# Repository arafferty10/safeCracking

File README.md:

# Team TAL: ATLS 4519 Safecracking Fall 2018
#### Repo for SafeCracking Class -- Using Arduino and manufactured parts to open a Sentry Safe Dial Safe

###### Successful Opening Video

## Information

Parts List - https://docs.google.com/spreadsheets/d/1XabOUtS-7bFRwG6XeN5u8nKVINY24XkEVGik6j0RJdE/edit?usp=sharing  
3D Printed Models - https://github.com/arafferty10/safeCracking/tree/master/models

## Personal Repos
* Lou - https://github.com/lume2651/safe-cracking 
* Aidan - https://github.com/arafferty10/personalSafeCracking
* Toby - https://github.com/towu1344/Safe-Cracking

## Images

---
Video of final opening: https://github.com/arafferty10/safeCracking/blob/master/img/IMG_3121.mp4

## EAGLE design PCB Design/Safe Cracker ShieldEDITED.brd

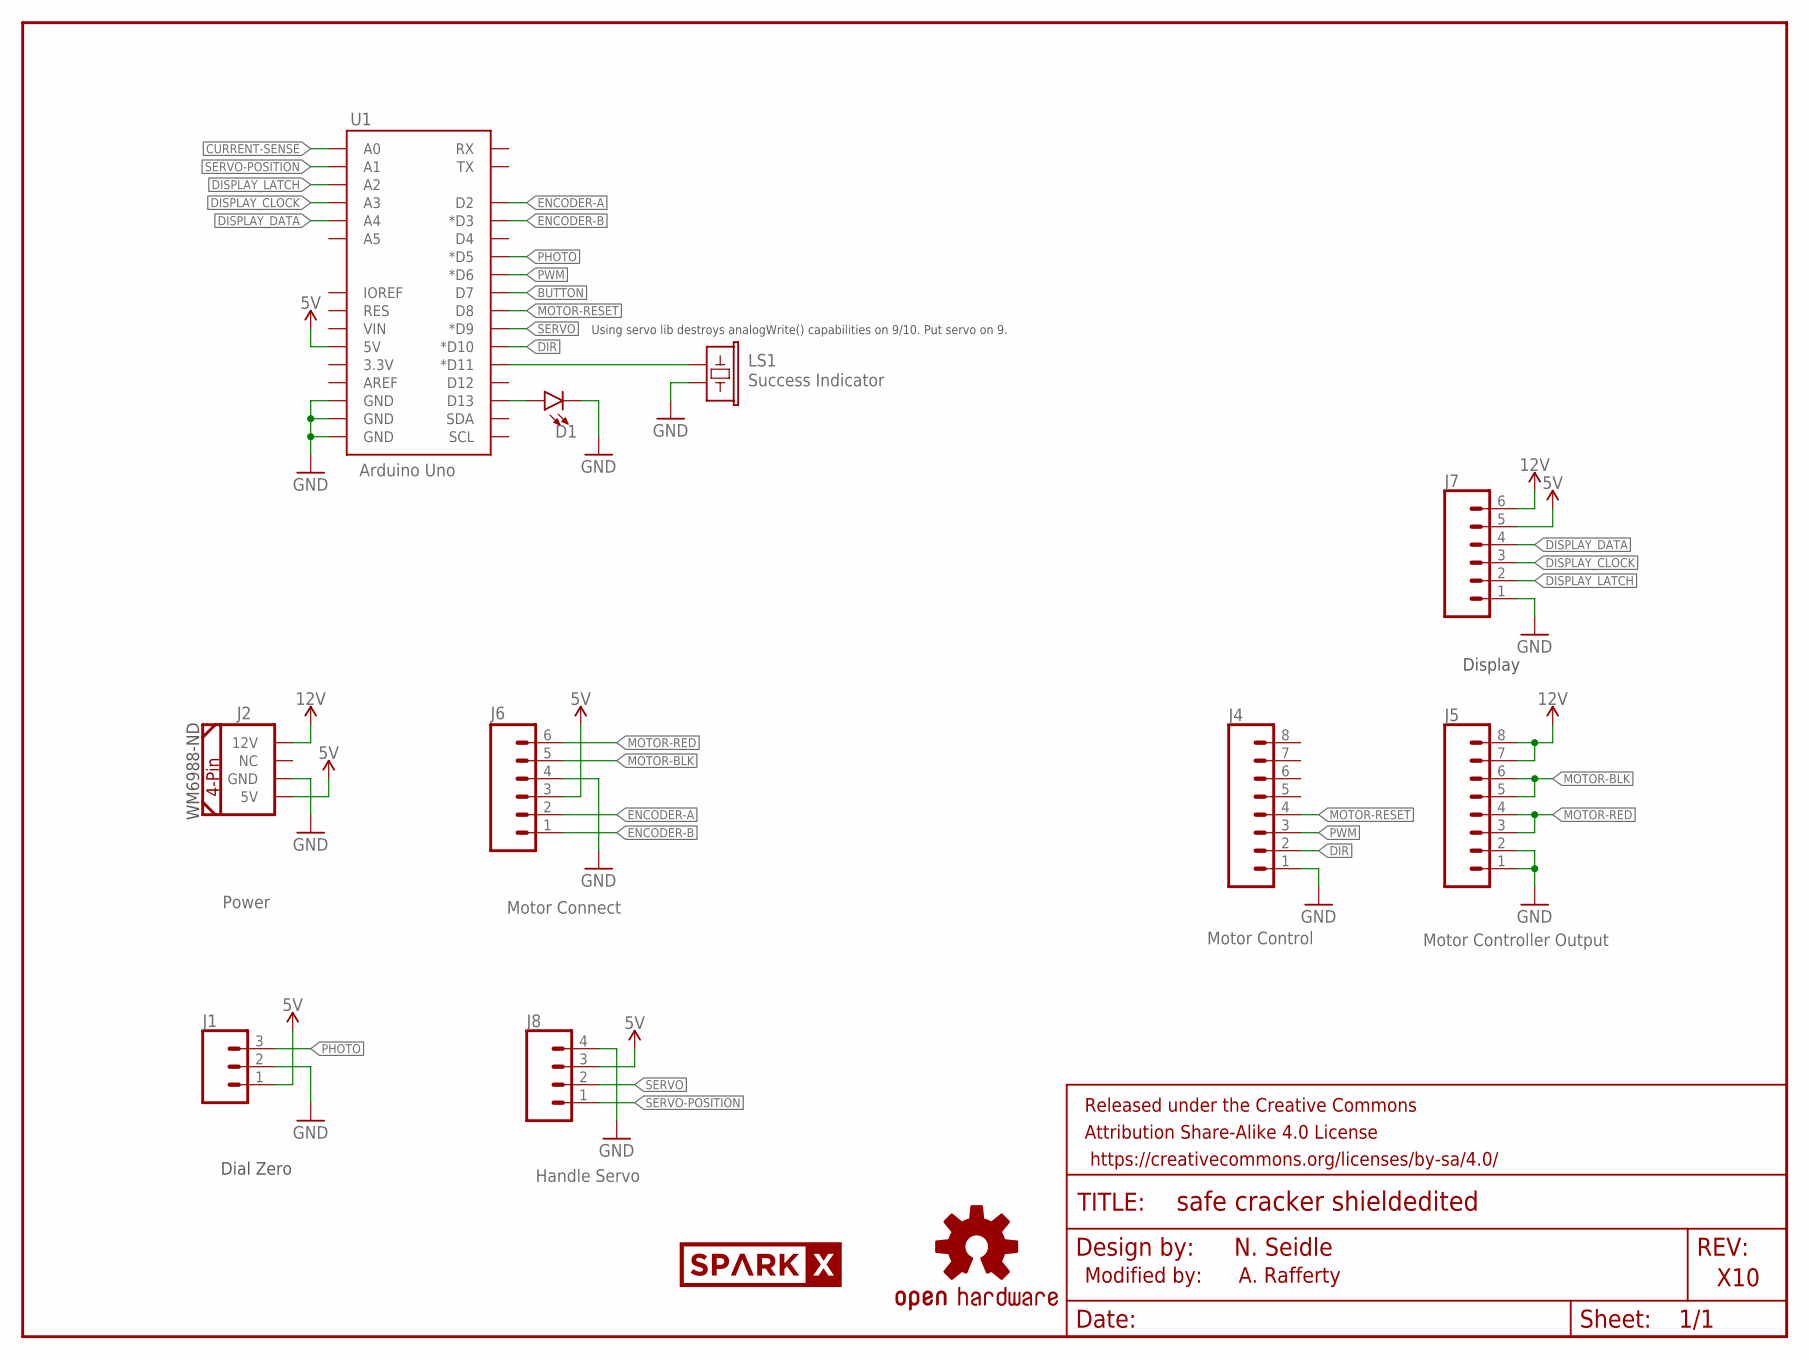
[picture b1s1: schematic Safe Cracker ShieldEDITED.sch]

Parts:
D1: LED5MM; LED_5MM
FRAME1: FRAME-LETTER; CREATIVE_COMMONS
J1: CONN_03JST-PTH-VERT; JST-3-PTH-VERT
J2: Power; COMPUTER-PERIPHERAL-POWER-RA
J4: Motor Control; 1X08
J5: Motor Controller Output; 1X08
J6: Motor Connect; 1X06@1
J7: CONN_06SILK_FEMALE_PTH; 1X06
J8: Handle Servo; 1X04
LOGO2: OSHW-LOGOS; OSHW-LOGO-S
LS1: Success Indicator; BUZZER-12MM
U1: Arduino Uno; UNO_R3_SHIELD_NOLABELS
U$1: SPARKX-LOGO5; SPARKX-LARGE

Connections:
5V: J1.1, J2.5V, J6.3, J7.5, J8.3, U1.5V
12V: J2.12V, J5.7, J5.8, J7.6
BUTTON: U1.D7
BUZZ: LS1.+ (1), U1.D11 (*D11)
CURRENT-SENSE: U1.A0
DIR: J4.2, U1.D10 (*D10)
DISPLAY_CLOCK: J7.3, U1.A3
DISPLAY_DATA: J7.4, U1.A4
DISPLAY_LATCH: J7.2, U1.A2
ENCODER-A: J6.2, U1.D2
ENCODER-B: J6.1, U1.D3 (*D3)
GND: D1.K (C), J1.2, J2.GND, J4.1, J5.1, J5.2, J6.4, J7.1, J8.4, LS1.- (2), U1.GND@0 (GND), U1.GND@1 (GND), U1.GND@2 (GND)
MOTOR-BLK: J5.5, J5.6, J6.5
MOTOR-RED: J5.3, J5.4, J6.6
MOTOR-RESET: J4.4, U1.D8
unnamed: D1.A, U1.D13
PHOTO: J1.3, U1.D5 (*D5)
PWM: J4.3, U1.D6 (*D6)
SERVO: J8.2, U1.D9 (*D9)
SERVO-POSITION: J8.1, U1.A1

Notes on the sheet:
WM6988-ND
N. Seidle
X10
Using servo lib destroys analogWrite() capabilities on 9/10. Put servo on 9.
Dial Zero
Display
Modified by: A. Rafferty

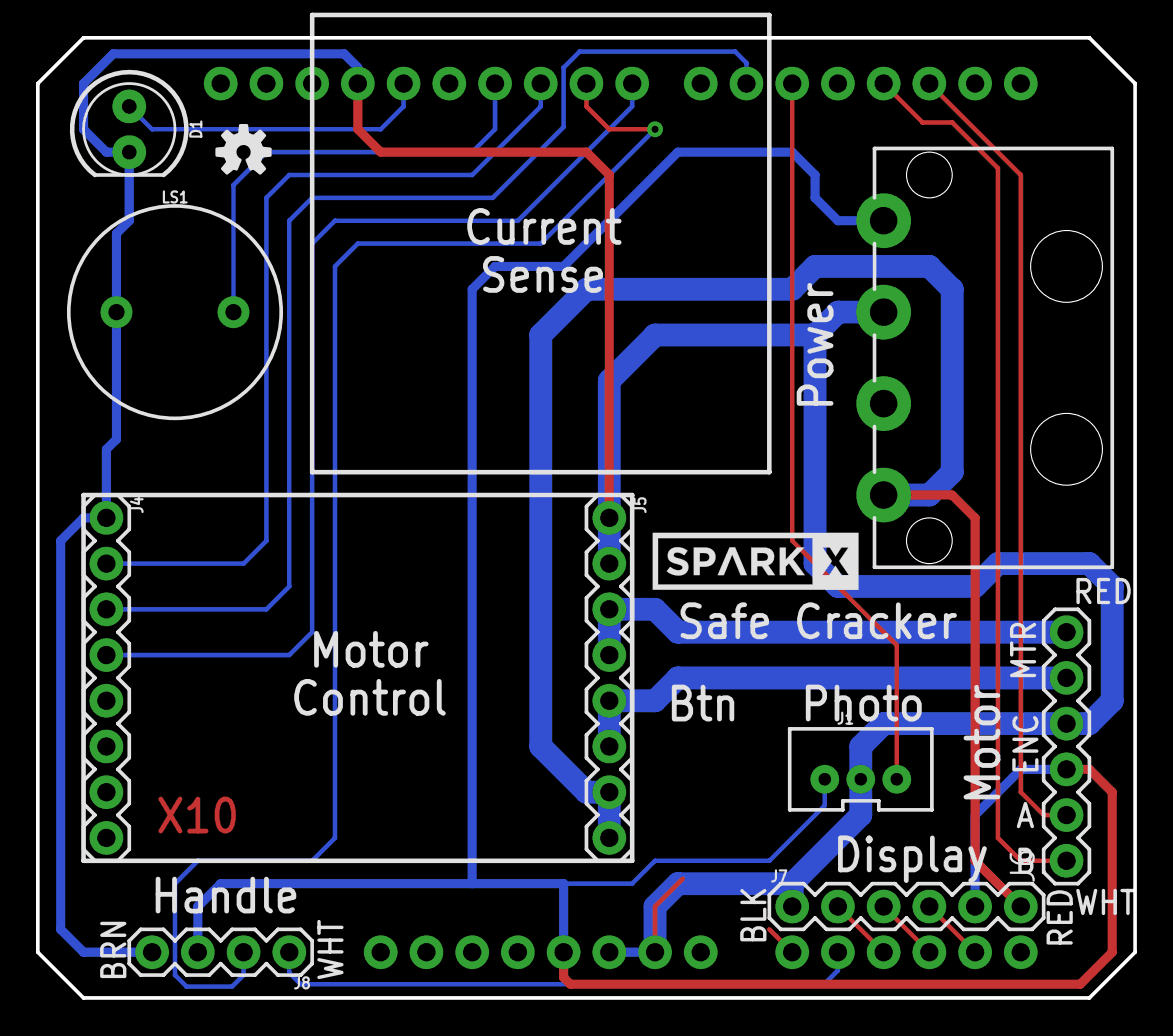
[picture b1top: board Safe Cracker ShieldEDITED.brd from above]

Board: 2 copper layers, 61.0 x 53.3 mm, 13 parts (0 on the bottom side), 18 nets.

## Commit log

2018-09-26 simple readMe update
2018-10-01 Add handle puller model
2018-10-01 Aidan Handle Design
2018-10-01 Toby Wu Handle Puller
2018-10-01 Toby Wu Control Motor
2018-10-03 add personal repo section
2018-10-09 add mainSketch folder
2018-10-09 add function templates
2018-10-09 menu scaffold
2018-10-09 personal git added
2018-10-09 new tab in mainSketch file
2018-10-09 add setDialSpeed()
2018-10-10 add EEPROM and Pin sections
2018-10-10 add motor control functions
2018-10-10 new main for if statements
2018-10-10 add Serial menu
2018-10-11 'fix' menu
2018-10-16 fix rotateCCW()
2018-10-17 cleanup rotateCCW() and add separate function file
2018-10-17 add encoderTest sketch folder
2018-10-17 test sketch for reading in encoder values
2018-10-17 add detectFlag()
2018-10-17 add detectFlag to menu
2018-10-23 setDial and manage home position
2018-10-23 commentz
2018-10-24 Starting Dial Value, go home
2018-10-29 PCB Designs
2018-10-31 servo header, changed serial rate
2018-11-25 add sketch for dial controls
2018-11-26 add basic motor control functions (on, off, turn CW/CCW) and function for detecting photogate
2018-11-26 add dial <-> encoder conversion functions
2018-11-26 add findFlag()
2018-11-26 add stepsRequired()
2018-11-26 add encoder count functions
2018-11-26 add gotoStep()
2018-11-26 add setDial()
2018-11-26 add resetDial()
2018-12-05 add serial menu and other stuff
2018-12-05 Coupler
2018-12-06 add a few test functions
2018-12-10 refractoring
2018-12-11 add dial position test function
2018-12-11 add initial eeprom read and first run initialization
2018-12-11 rename functions.ino to primaryFunctions.ino
2018-12-11 add measureDiscC and measureIndents functions
2018-12-11 finish measureFunctions
2018-12-12 ReadMe Models
2018-12-15 add photos
2018-12-15 Revert "add photos"
    This reverts commit d224561b4f8bf672d165ef35202d130146be8ae8.
2018-12-15 add video of opening safe
2018-12-15 add pictures
2018-12-15 right side up?
2018-12-15 attempting to embed youtube video
2018-12-15 modified for youtube embed
2018-12-15 adding images to README
2018-12-15 more photos and small README changes
2018-12-15 small formatting changed to README
2018-12-15 tiny README change

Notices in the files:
parts and their libraries:
SparkFun-Aesthetics: Licensing: CC v3.0 Share-Alike You are welcome to use this library for commercial purposes.
SparkFun-Aesthetics: Released under the Creative Commons Attribution Share-Alike 4.0 License
SparkFun-Aesthetics: https://creativecommons.org/licenses/by-sa/4.0
